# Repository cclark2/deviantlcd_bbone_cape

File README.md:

DeviantLCD BeagleBone Cape
==========================

Stick it to standards and bit-bang an LCD interface! This cape features a 240x320 LCD with touchscreen connected to the BeagleBone PRU and GPIOs. Use it when you can't spare the BeagleBone's LCD interface pins for a regular display cape.

Special thanks to <a href="http://www.sparkfun.com/">SparkFun</a> for use of their open-source EAGLE libraries.

## Project Links
- <a href="http://www.hitchhikeree.org/beaglebone_capes/deviantlcd/">HitchhikerEE page</a>
- <a href="http://www.youtube.com/watch?v=hFeXr79dWaM">YouTube video</a>
- <a href="https://docs.google.com/folder/d/0B5HjtPsFD8u5RnRneGhOc2xUcGM/edit">Design files on Google Drive</a>
- <a href="http://beagleboard.org/CapeContest/entries/DeviantLCD/">BeagleBone Cape Contest page</a>

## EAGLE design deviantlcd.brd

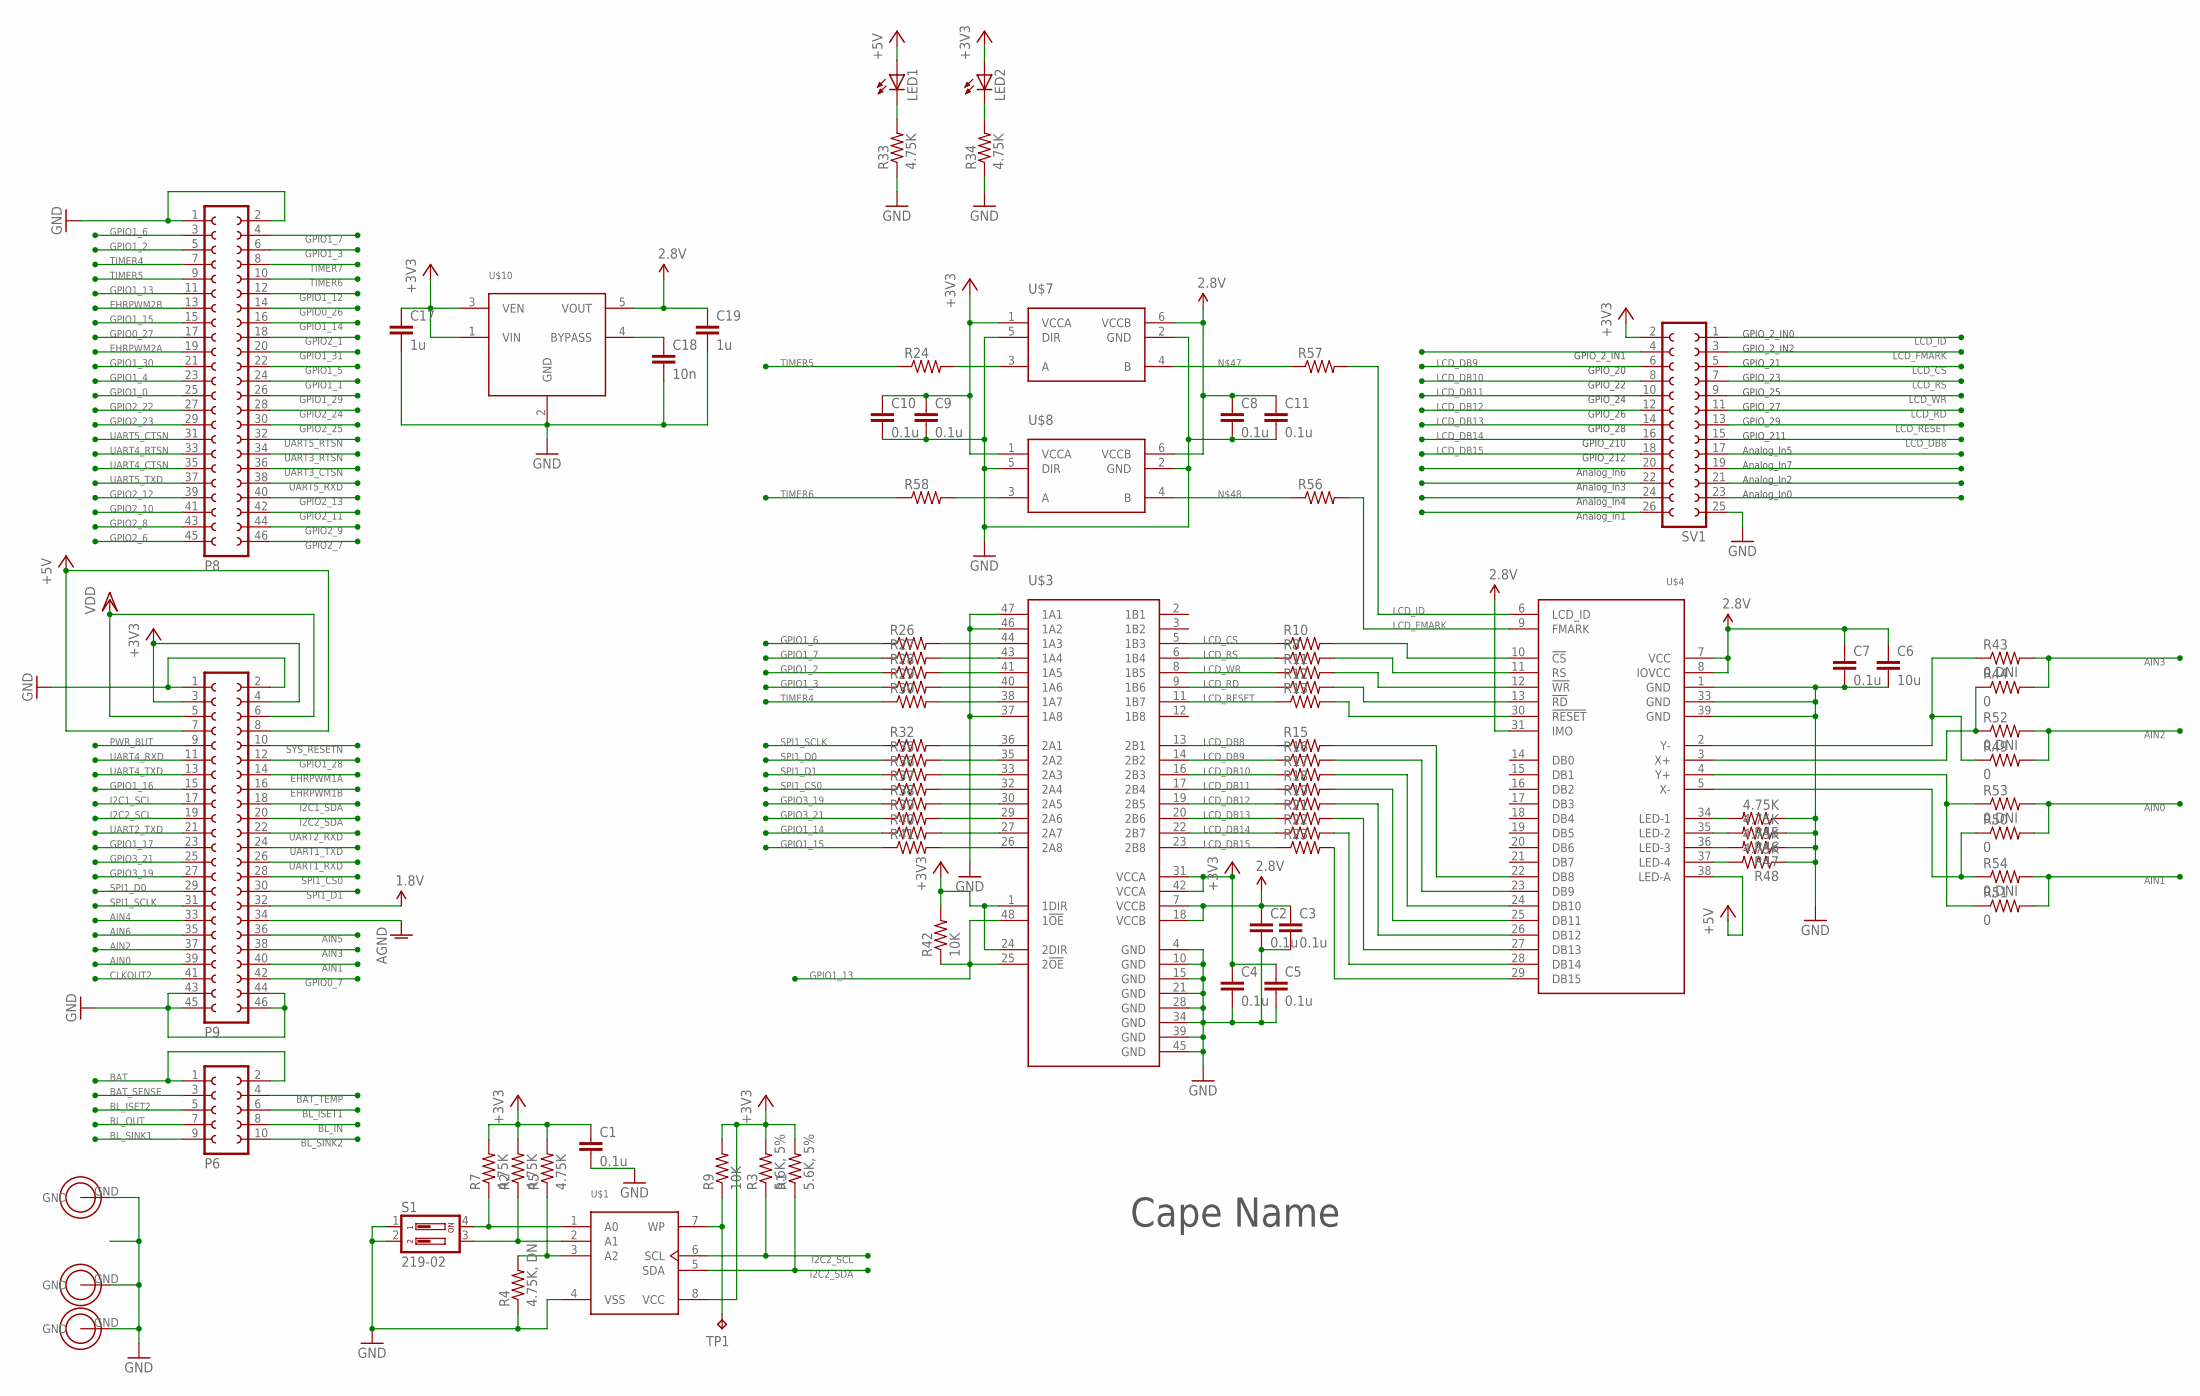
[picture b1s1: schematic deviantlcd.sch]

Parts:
C1, C2, C3, C4, C5, C7, C8, C9, C10, C11: 0.1u; C0603
C6: 10u; C0603
C17, C19: 1u; C0603
C18: 10n; C0603
H1, H3, H4: HOLE
LED1, LED2: LEDCHIPLED_0603; CHIPLED_0603
P6: FE05-2
P8, P9: FE23-2
R1, R3: 5.6K, 5%; R0603
R2, R5, R7, R33, R34, R45, R46, R47, R48: 4.75K; R0603
R4: 4.75K, DNI; R0603
R8, R10, R11, R12, R13, R15, R16, R17, R18, R19, R21, R22, R23, R24, R26, R27, R28, R29, R30, R32, R35, R36, R37, R38, R39, R40, R41, R56, R57, R58: R-US_R0402; R0402
R9: 10K; R0603
R42: 10K; R0402
R43, R52, R53, R54: 0,DNI; R0402
R44, R49, R50, R51: 0; R0402
S1: 219-02; CTS-219-02
SV1: FE13-2
TP1: TPB2,54; B2,54
U$1: CAT24C256; SOIC8
U$3: SN74LVCH16T245; TSSOP48
U$4: NHD-2.4-240320SF-CTXI
U$7, U$8: SN74LVC1T45; SOT23-6
U$10: LP3985; SOT23-5

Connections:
1.8V: P9.32
2.85V: C6.1, C7.1, C8.1, C11.1, C19.1, U$4.7 (VCC), U$4.8 (IOVCC), U$4.31 (IMO), U$7.6 (VCCB), U$8.6 (VCCB), U$10.5 (VOUT)
+3V3: C1.1, C4.1, C5.1, C9.1, C10.1, C17.1, LED2.A, P9.3, P9.4, R1.2, R2.2, R3.2, R5.2, R7.2, R9.2, R42.2, SV1.2, U$1.8 (VCC), U$3.1 (1DIR), U$3.24 (2DIR), U$3.31 (VCCA), U$3.42 (VCCA), U$7.1 (VCCA), U$8.1 (VCCA), U$10.1 (VIN), U$10.3 (VEN)
+5V: LED1.A, P9.7, P9.8, U$4.38 (LED-A)
AGND: P9.34
AIN0: P9.39, R50.2, R53.2
AIN1: P9.40, R51.2, R54.2
AIN2: P9.37, R49.2, R52.2
AIN3: P9.38, R43.2, R44.2
AIN4: P9.33
AIN5: P9.36
AIN6: P9.35
BAT: P6.1, P6.2
BAT_SENSE: P6.3
BAT_TEMP: P6.4
BL_IN: P6.8
BL_ISET1: P6.6
BL_ISET2: P6.5
BL_OUT: P6.7
BL_SINK1: P6.9
BL_SINK2: P6.10
CLKOUT2: P9.41
EHRPWM1A: P9.14
EHRPWM1B: P9.16
EHRPWM2A: P8.19
EHRPWM2B: P8.13
FF: SV1.4
GND: C1.2, C2.2, C3.2, C4.2, C5.2, C6.2, C7.2, C8.2, C9.2, C10.2, C11.2, C17.2, C18.2, C19.2, H1.GND, H3.GND, H4.GND, P8.1, P8.2, P9.1, P9.2, P9.43, P9.44, P9.45, P9.46, R4.1, R33.1, R34.1, R45.1, R46.1, R47.1, R48.1, S1.1, S1.2, SV1.25, U$1.4 (VSS), U$3.4 (GND), U$3.10 (GND), U$3.15 (GND), U$3.21 (GND), U$3.28 (GND), U$3.34 (GND), U$3.37 (1A8), U$3.39 (GND), U$3.45 (GND), U$3.46 (1A2), U$3.47 (1A1), U$4.1 (GND), U$4.33 (GND), U$4.39 (GND), U$7.2 (GND), U$7.5 (DIR), U$8.2 (GND), U$8.5 (DIR), U$10.2 (GND)
GPIO0_7: P9.42
GPIO0_26: P8.14
GPIO0_27: P8.17
GPIO1_0: P8.25
GPIO1_1: P8.24
GPIO1_2: P8.5, R28.1
GPIO1_3: P8.6, R29.1
GPIO1_4: P8.23
GPIO1_5: P8.22
GPIO1_6: P8.3, R26.1
GPIO1_7: P8.4, R27.1
GPIO1_12: P8.12
GPIO1_13: P8.11, R42.1, U$3.25 (2!OE), U$3.48 (1!OE)
GPIO1_14: P8.16, R40.1
GPIO1_15: P8.15, R41.1
GPIO1_16: P9.15
GPIO1_17: P9.23
GPIO1_28: P9.12
GPIO1_29: P8.26
GPIO1_30: P8.21
GPIO1_31: P8.20
GPIO2_1: P8.18
GPIO2_6: P8.45
GPIO2_7: P8.46
GPIO2_8: P8.43
GPIO2_9: P8.44
GPIO2_10: P8.41
GPIO2_11: P8.42
GPIO2_12: P8.39
GPIO2_13: P8.40
GPIO2_22: P8.27
GPIO2_23: P8.29
GPIO2_24: P8.28
GPIO2_25: P8.30
GPIO3_19: P9.27, R38.1
GPIO3_21: P9.25, R39.1
I2C1_SCL: P9.17
I2C1_SDA: P9.18
I2C2_SCL: P9.19, R3.1, U$1.6 (SCL)
I2C2_SDA: P9.20, R1.1, U$1.5 (SDA)
LCD_CS: R10.1, SV1.5, U$3.5 (1B3)
LCD_DB8: R15.1, SV1.15, U$3.13 (2B1)
LCD_DB9: R16.1, SV1.6, U$3.14 (2B2)
LCD_DB10: R17.1, SV1.8, U$3.16 (2B3)
LCD_DB11: R18.1, SV1.10, U$3.17 (2B4)
LCD_DB12: R19.1, SV1.12, U$3.19 (2B5)
LCD_DB13: R21.1, SV1.14, U$3.20 (2B6)
LCD_DB14: R22.1, SV1.16, U$3.22 (2B7)
LCD_DB15: R23.1, SV1.18, U$3.23 (2B8)
LCD_FMARK: R56.2, SV1.3, U$4.9 (FMARK)
LCD_ID: R57.2, SV1.1, U$4.6 (LCD_ID)
LCD_RD: R12.1, SV1.11, U$3.9 (1B6)
LCD_RESET: R13.1, SV1.13, U$3.11 (1B7)
LCD_RS: R8.1, SV1.7, U$3.6 (1B4)
LCD_WR: R11.1, SV1.9, U$3.8 (1B5)
unnamed: R7.1, S1.4, U$1.1 (A0)
unnamed: R2.1, S1.3, U$1.2 (A1)
unnamed: R4.2, R5.1, U$1.3 (A2)
unnamed: R9.1, TP1.TP, U$1.7 (WP)
unnamed: LED1.C, R33.2
unnamed: LED2.C, R34.2
unnamed: R24.2, U$7.3 (A)
unnamed: R58.2, U$8.3 (A)
unnamed: R26.2, U$3.44 (1A3)
unnamed: R27.2, U$3.43 (1A4)
unnamed: R28.2, U$3.41 (1A5)
unnamed: R29.2, U$3.40 (1A6)
unnamed: R30.2, U$3.38 (1A7)
unnamed: R32.2, U$3.36 (2A1)
unnamed: R35.2, U$3.35 (2A2)
unnamed: R36.2, U$3.33 (2A3)
unnamed: R37.2, U$3.32 (2A4)
unnamed: R38.2, U$3.30 (2A5)
unnamed: R39.2, U$3.29 (2A6)
unnamed: R40.2, U$3.27 (2A7)
unnamed: R41.2, U$3.26 (2A8)
unnamed: R57.1, U$7.4 (B)
unnamed: R56.1, U$8.4 (B)
unnamed: R10.2, U$4.10 (!CS)
unnamed: R8.2, U$4.11 (RS)
unnamed: R11.2, U$4.12 (!WR)
unnamed: R12.2, U$4.13 (!RD)
unnamed: R13.2, U$4.30 (!RESET)
unnamed: R23.2, U$4.29 (DB15)
unnamed: R22.2, U$4.28 (DB14)
unnamed: R21.2, U$4.27 (DB13)
unnamed: R19.2, U$4.26 (DB12)
unnamed: R18.2, U$4.25 (DB11)
unnamed: R17.2, U$4.24 (DB10)
unnamed: R16.2, U$4.23 (DB9)
unnamed: R15.2, U$4.22 (DB8)
unnamed: C18.1, U$10.4 (BYPASS)
unnamed: R45.2, U$4.34 (LED-1)
unnamed: R46.2, U$4.35 (LED-2)
unnamed: R47.2, U$4.36 (LED-3)
unnamed: R48.2, U$4.37 (LED-4)
unnamed: R43.1, R49.1, U$4.2 (Y-)
unnamed: R44.1, R52.1, U$4.3 (X+)
unnamed: R51.1, R53.1, U$4.4 (Y+)
unnamed: R50.1, R54.1, U$4.5 (X-)
PWR_BUT: P9.9
SPI1_CS0: P9.28, R37.1
SPI1_D0: P9.29, R35.1
SPI1_D1: P9.30, R36.1
SPI1_SCLK: P9.31, R32.1
SYS_RESETN: P9.10
TIMER4: P8.7, R30.1
TIMER5: P8.9, R24.1
TIMER6: P8.10, R58.1
TIMER7: P8.8
UART1_RXD: P9.26
UART1_TXD: P9.24
UART2_RXD: P9.22
UART2_TXD: P9.21
UART3_CTSN: P8.36
UART3_RTSN: P8.34
UART4_CTSN: P8.35
UART4_RTSN: P8.33
UART4_RXD: P9.11
UART4_TXD: P9.13
UART5_CTSN: P8.31
UART5_RTSN: P8.32
UART5_RXD: P8.38
UART5_TXD: P8.37
VCCB@2: C2.1, C3.1, U$3.7 (VCCB), U$3.18 (VCCB)
VDD: P9.5, P9.6

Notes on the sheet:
Cape Name
GPIO_2_IN1
GPIO_20
GPIO_22
GPIO_24
GPIO_26
GPIO_28
GPIO_210
GPIO_212
Analog_In6
Analog_In3
Analog_In4
Analog_In1
GPIO_2_IN0
GPIO_2_IN2
GPIO_21
GPIO_23
GPIO_25
GPIO_27
GPIO_29
GPIO_211
Analog_In5
Analog_In7
Analog_In2
Analog_In0

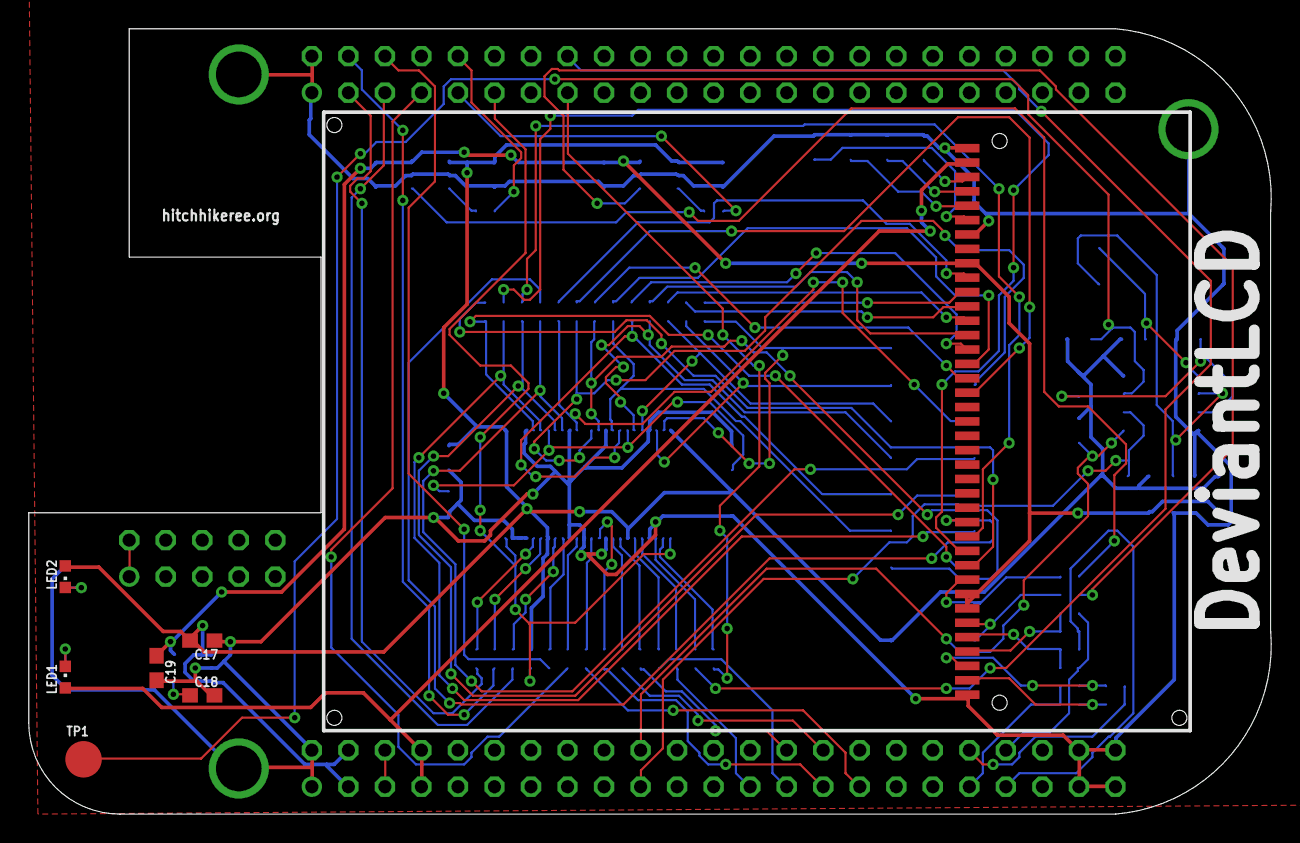
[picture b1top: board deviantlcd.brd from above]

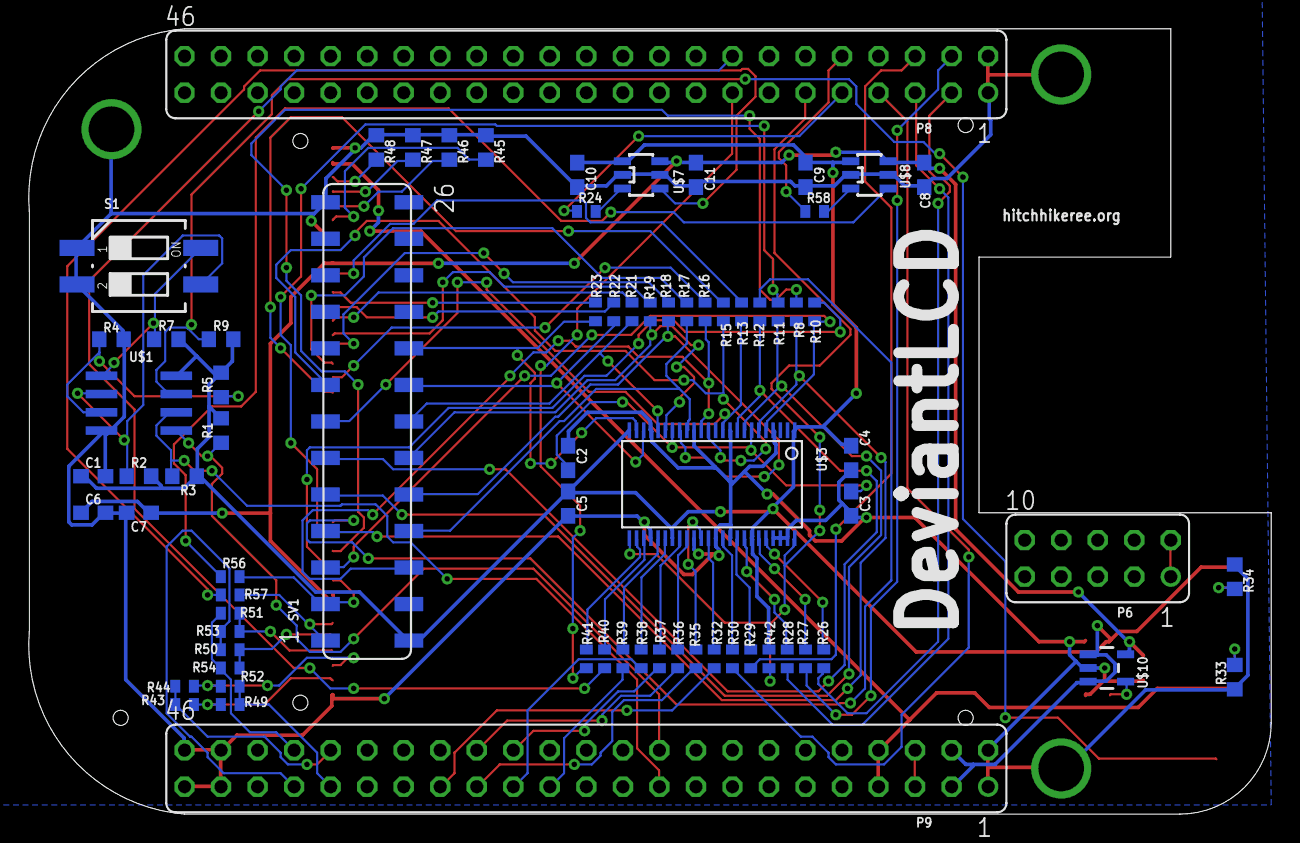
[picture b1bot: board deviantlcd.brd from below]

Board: 2 copper layers, 86.4 x 54.6 mm, 83 parts (73 on the bottom side), 89 nets.

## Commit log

2013-01-01 Design complete, cleanup needed.
2013-01-01 BOM done.
2013-01-06 Added BOM prices, added PDFs of design, sorted files.
2013-01-06 BOM prices for real this time.
2013-01-06 Fixing BOM formatting.
